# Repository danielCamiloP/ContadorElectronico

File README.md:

# ContadorElectronico
Diseño de contador electrónico para Sensores y Actuadores

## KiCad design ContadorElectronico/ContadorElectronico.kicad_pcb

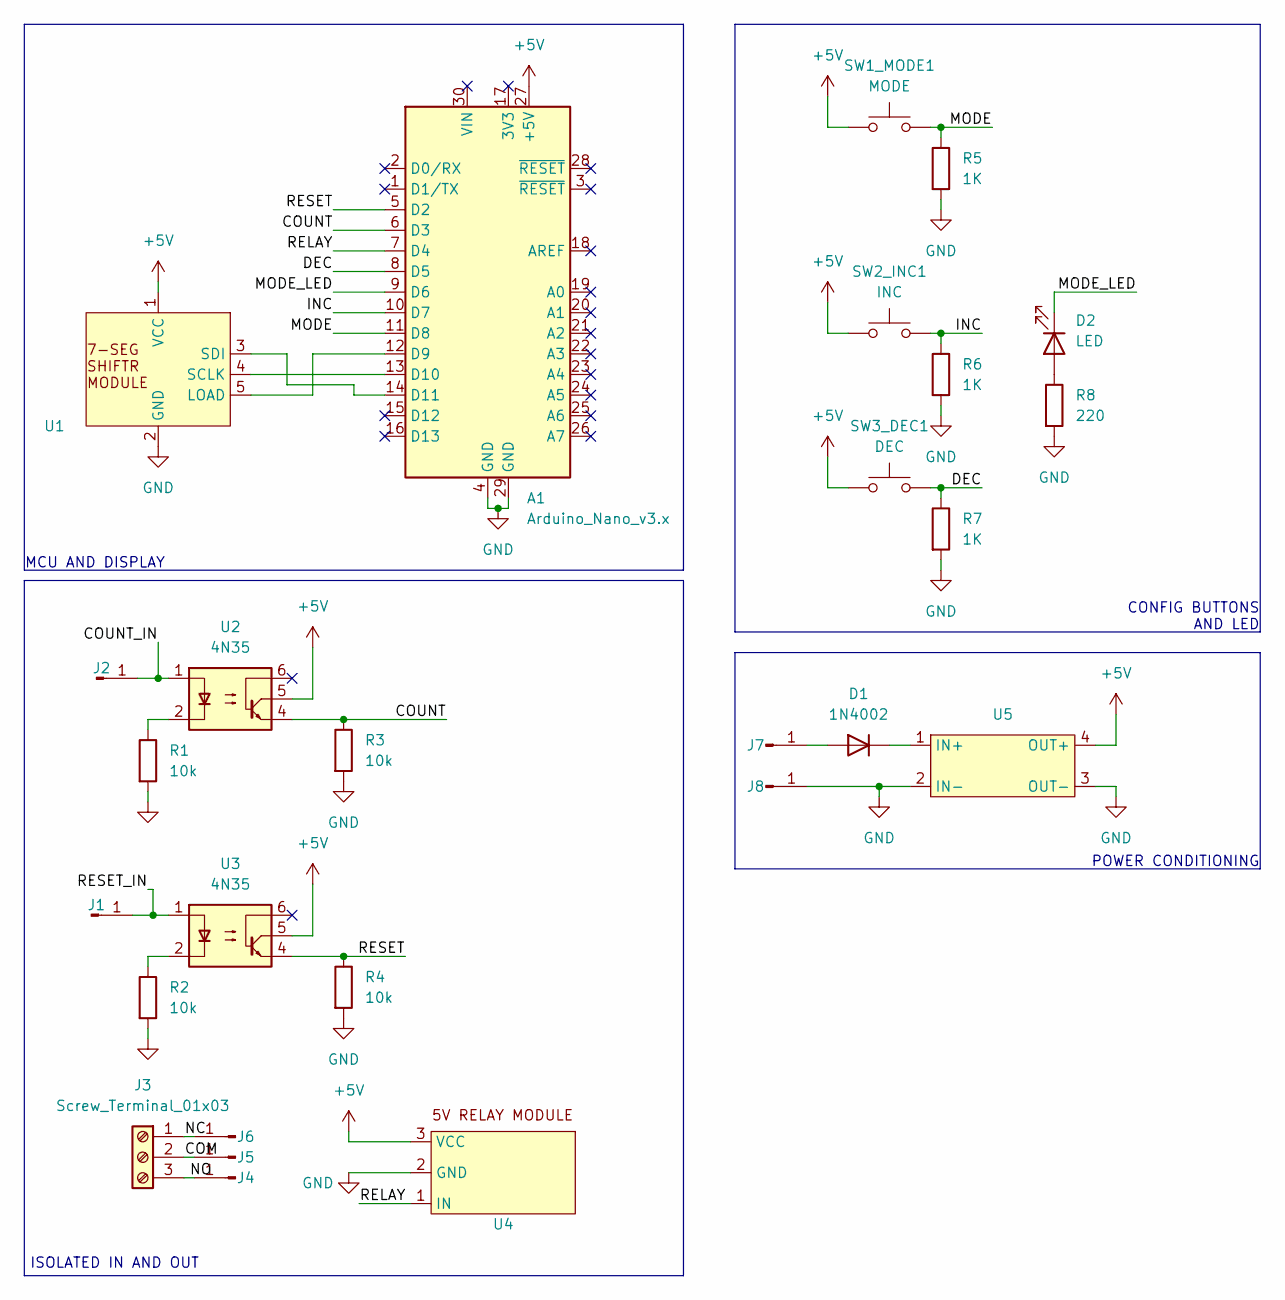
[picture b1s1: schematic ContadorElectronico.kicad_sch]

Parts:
A1: Arduino_Nano_v3.x; Arduino_Nano
D1: 1N4002; D_DO-41_SOD81_P10.16mm_Horizontal
D2: LED; LED_D3.0mm
J1, J2, J4, J5, J6, J7, J8: Conn_01x01_Pin; Banana_Jack_1Pin
J3: Screw_Terminal_01x03; TerminalBlock_bornier-3_P5.08mm
R1, R2, R3, R4: 10k; R_1206_3216Metric_Pad1.30x1.75mm_HandSolder
R5, R6, R7: 1K; R_1206_3216Metric_Pad1.30x1.75mm_HandSolder
R8: 220; R_1206_3216Metric_Pad1.30x1.75mm_HandSolder
SW1_MODE1: MODE; SW_PUSH_6mm
SW2_INC1: INC; SW_PUSH_6mm
SW3_DEC1: DEC; SW_PUSH_6mm
U1: 2Digit7SEG
U2, U3: 4N35; DIP-6_W7.62mm
U4: PinSocket_1x03_P2.54mm_Vertical
U5: LM2596 MODULE

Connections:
+5V: A1.27 (+5V), SW1_MODE1.1, SW2_INC1.1, SW3_DEC1.1, U1.1 (VCC), U2.5, U3.5, U4.3 (VCC), U5.4 (OUT+)
/COM: J3.2, J5.1
/COUNT: A1.6 (D3), R3.1, U2.4
/COUNT_IN: J2.1, U2.1
/DEC: A1.8 (D5), R7.1, SW3_DEC1.2
/INC: A1.10 (D7), R6.1, SW2_INC1.2
/MODE: A1.11 (D8), R5.1, SW1_MODE1.2
/MODE_LED: A1.9 (D6), D2.1 (K)
/NC: J3.1, J6.1
/NO: J3.3, J4.1
/RELAY: A1.7 (D4), U4.1 (IN)
/RESET: A1.5 (D2), R4.1, U3.4
/RESET_IN: J1.1, U3.1
GND: A1.4 (GND), A1.29 (GND), J8.1, R1.2, R2.2, R3.2, R4.2, R5.2, R6.2, R7.2, R8.2, U1.2 (GND), U4.2 (GND), U5.2 (IN-), U5.3 (OUT-)
unnamed: A1.12 (D9), U1.5 (LOAD)
unnamed: A1.13 (D10), U1.4 (SCLK)
unnamed: A1.14 (D11), U1.3 (SDI)
unnamed: D1.2 (A), J7.1
unnamed: D1.1 (K), U5.1 (IN+)
unnamed: D2.2 (A), R8.1
unnamed: R1.1, U2.2
unnamed: R2.1, U3.2

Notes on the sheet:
MCU AND DISPLAY
CONFIG BUTTONS AND LED
POWER CONDITIONING
ISOLATED IN AND OUT

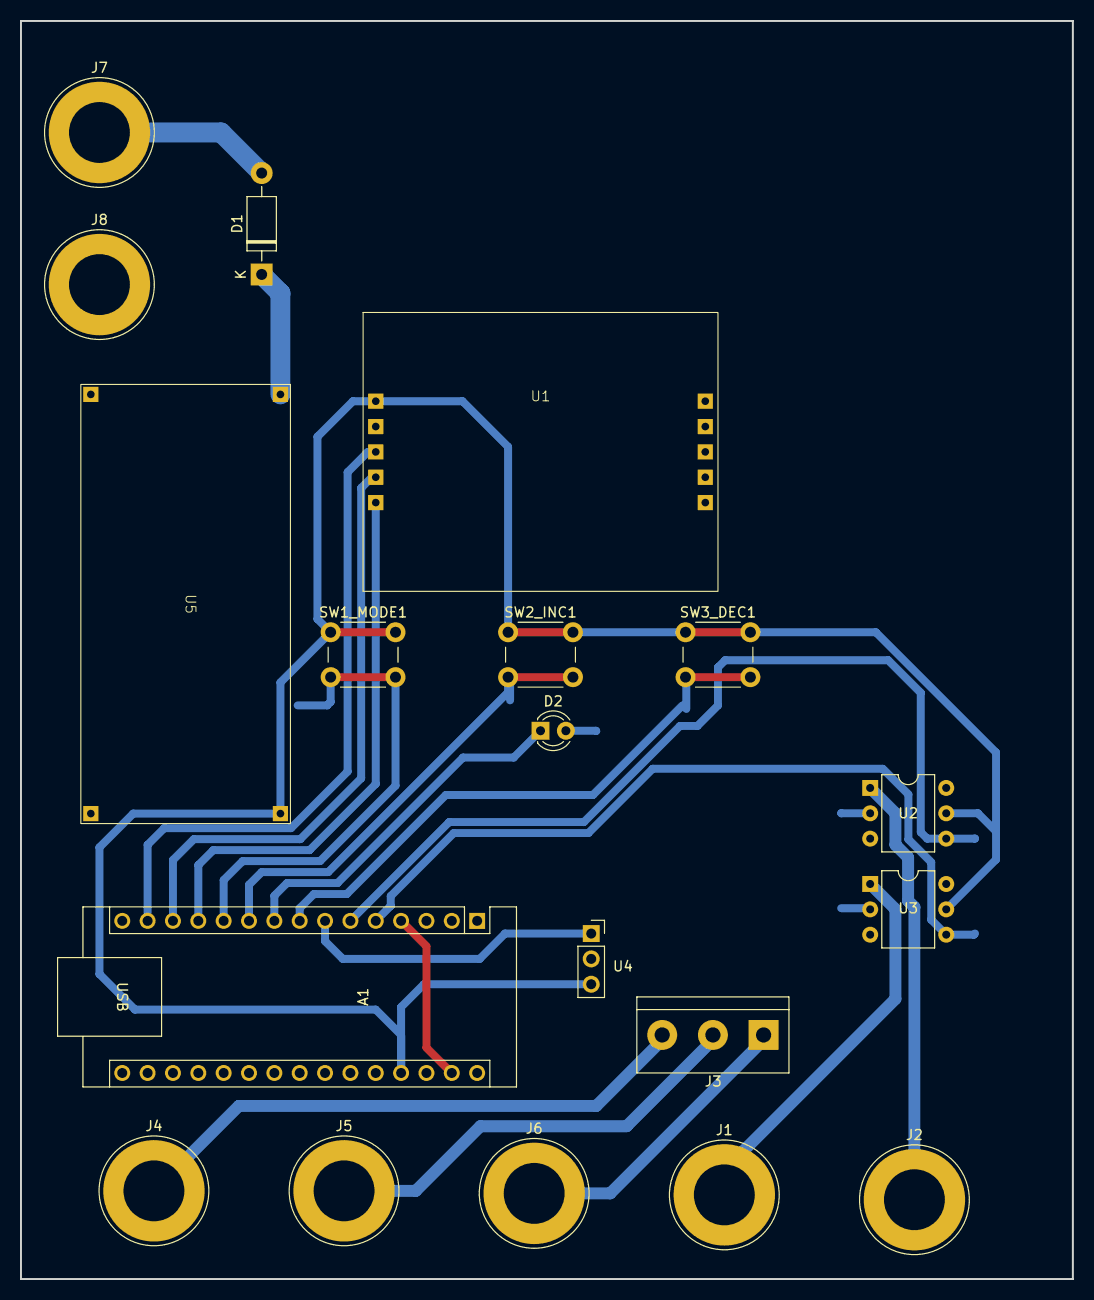
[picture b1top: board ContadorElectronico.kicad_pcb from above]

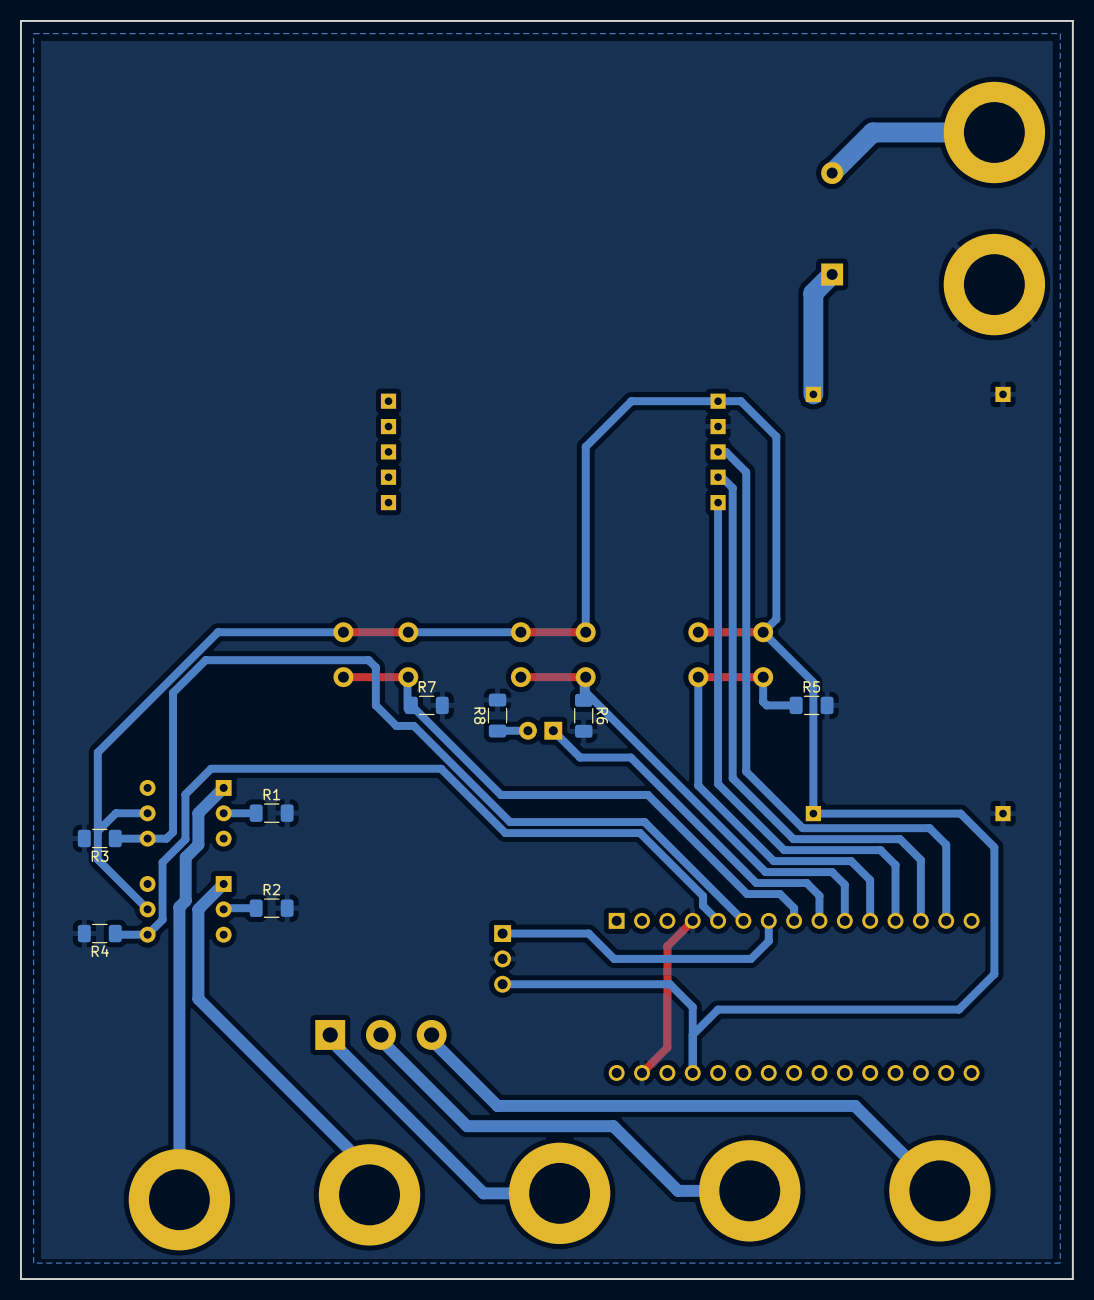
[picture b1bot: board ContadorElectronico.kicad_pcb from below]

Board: 2 copper layers, 105.4 x 126.1 mm, 27 parts (8 on the bottom side), 22 nets.

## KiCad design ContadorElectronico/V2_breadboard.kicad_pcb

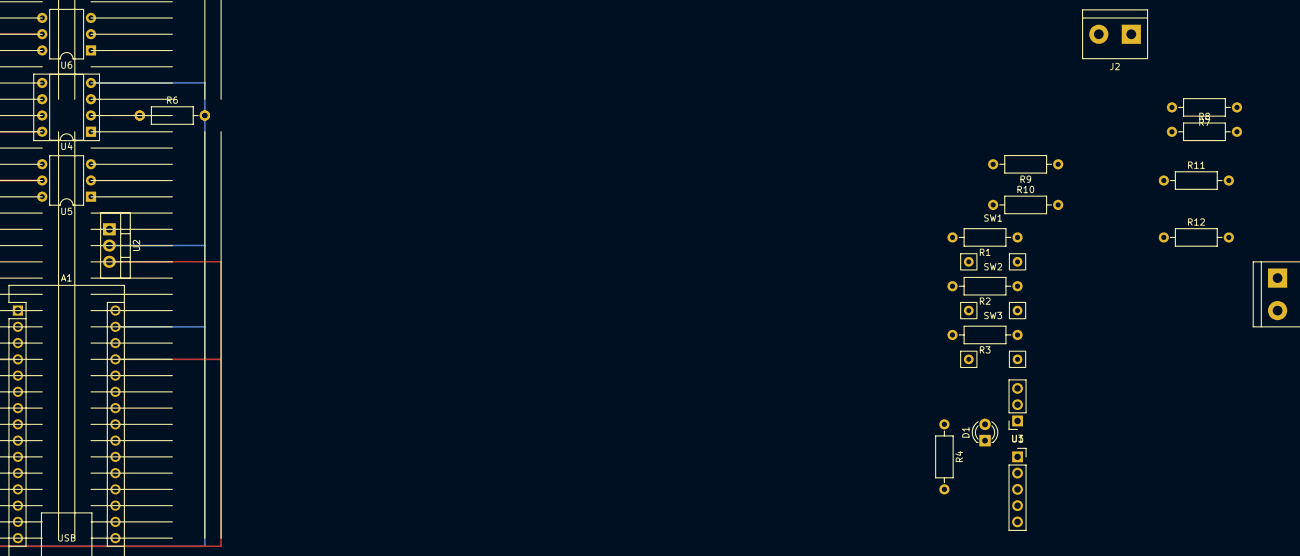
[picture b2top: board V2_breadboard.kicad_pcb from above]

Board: 2 copper layers, 25 parts (1 on the bottom side), 22 nets.

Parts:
A1: Arduino_Nano_v3.x; Arduino_Nano
D1: LED; LED_D3.0mm
J1, J2: Screw_Terminal_01x02; TerminalBlock_bornier-2_P5.08mm
R1, R2, R3: 1K; R_Axial_DIN0207_L6.3mm_D2.5mm_P10.16mm_Horizontal
R4, R9, R10: 220; R_Axial_DIN0207_L6.3mm_D2.5mm_P10.16mm_Horizontal
R5, R7, R11, R12: 10k; R_Axial_DIN0207_L6.3mm_D2.5mm_P10.16mm_Horizontal
R6, R8: 100; R_Axial_DIN0207_L6.3mm_D2.5mm_P10.16mm_Horizontal
SW1: MODE; SW Header
SW2: INC; SW Header
SW3: DEC; SW Header
U1: PinSocket_1x05_P2.54mm_Vertical
U2: L7805; TO-220-3_Vertical
U3: PinSocket_1x03_P2.54mm_Vertical
U4: LM358; DIP-8_W7.62mm_Socket
U5, U6: 4N35; DIP-6_W7.62mm

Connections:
+5V: A1.27 (+5V), R5.1, R7.1, SW1.1, SW2.1, SW3.1, U1.1 (VCC), U2.3 (OUT), U3.3 (VCC), U4.8 (V+), U5.5, U6.5
/COUNT: A1.5 (D2), R11.1, U5.4
/COUNT_IN: J2.2, U4.3 (+)
/DEC: A1.9 (D6), R3.1, SW3.2
/INC: A1.8 (D5), R2.1, SW2.2
/MODE: A1.7 (D4), R1.1, SW1.2
/MODE_LED: A1.11 (D8), D1.1 (K)
/RELAY: A1.10 (D7), U3.1 (IN)
/RESET: A1.6 (D3), R12.1, U6.4
/RESET_IN: J2.1, U4.5 (+)
GND: A1.4 (GND), A1.29 (GND), J1.2, R1.2, R2.2, R3.2, R4.2, R6.2, R8.2, R9.2, R10.2, R11.2, R12.2, U1.2 (GND), U2.2 (GND), U3.2 (GND), U4.4 (V-)
unnamed: A1.12 (D9), U1.3 (SDI)
unnamed: A1.13 (D10), U1.4 (SCLK)
unnamed: A1.14 (D11), U1.5 (LOAD)
unnamed: D1.2 (A), R4.1
unnamed: J1.1, U2.1 (IN)
unnamed: R9.1, U5.2
unnamed: R10.1, U6.2
unnamed: U4.1, U5.1
unnamed: U4.7, U6.1
unnamed: R5.2, R6.1, U4.2 (-)
unnamed: R7.2, R8.1, U4.6 (-)

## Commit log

2024-01-08 Subida inicial de archivos para revisión de versiones
2024-01-09 Minor changes
2024-01-12 Creación simbolo regulador 2596
2024-01-15 MinorChanges
2024-01-16 First PCB design
2024-01-17 PCB done, 5V direct to Arduino
2024-01-17 PCB con tolerancias adecuadas
2024-01-18 Added 3D models for PCB
2024-01-22 Diseño inicial
2024-01-23 Agregado plano de tierra
2024-01-24 Removed opamp from Schematic
2024-01-24 PCB design with 3 pin bornier
2024-01-24 2 Pin Bornier for inputs
2024-01-24 Fixed 3D Models for borniers and terminals
2024-01-24 Cambios varios
2024-01-25 Working version #1
2024-01-25 ajustes a la PCB
2024-02-02 Add codigo arduino funcional
